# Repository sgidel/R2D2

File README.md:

Repository for R2D2 remote control and management

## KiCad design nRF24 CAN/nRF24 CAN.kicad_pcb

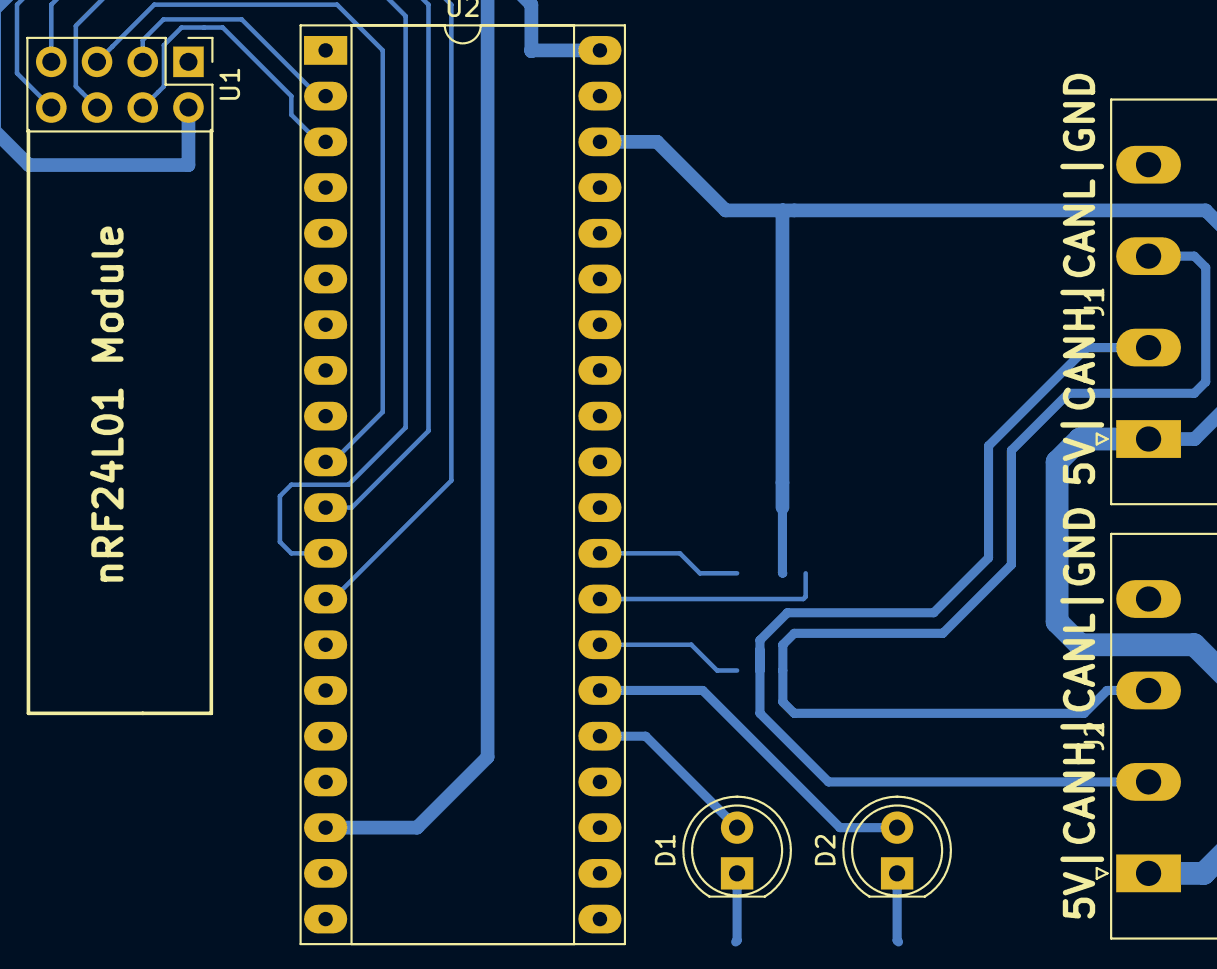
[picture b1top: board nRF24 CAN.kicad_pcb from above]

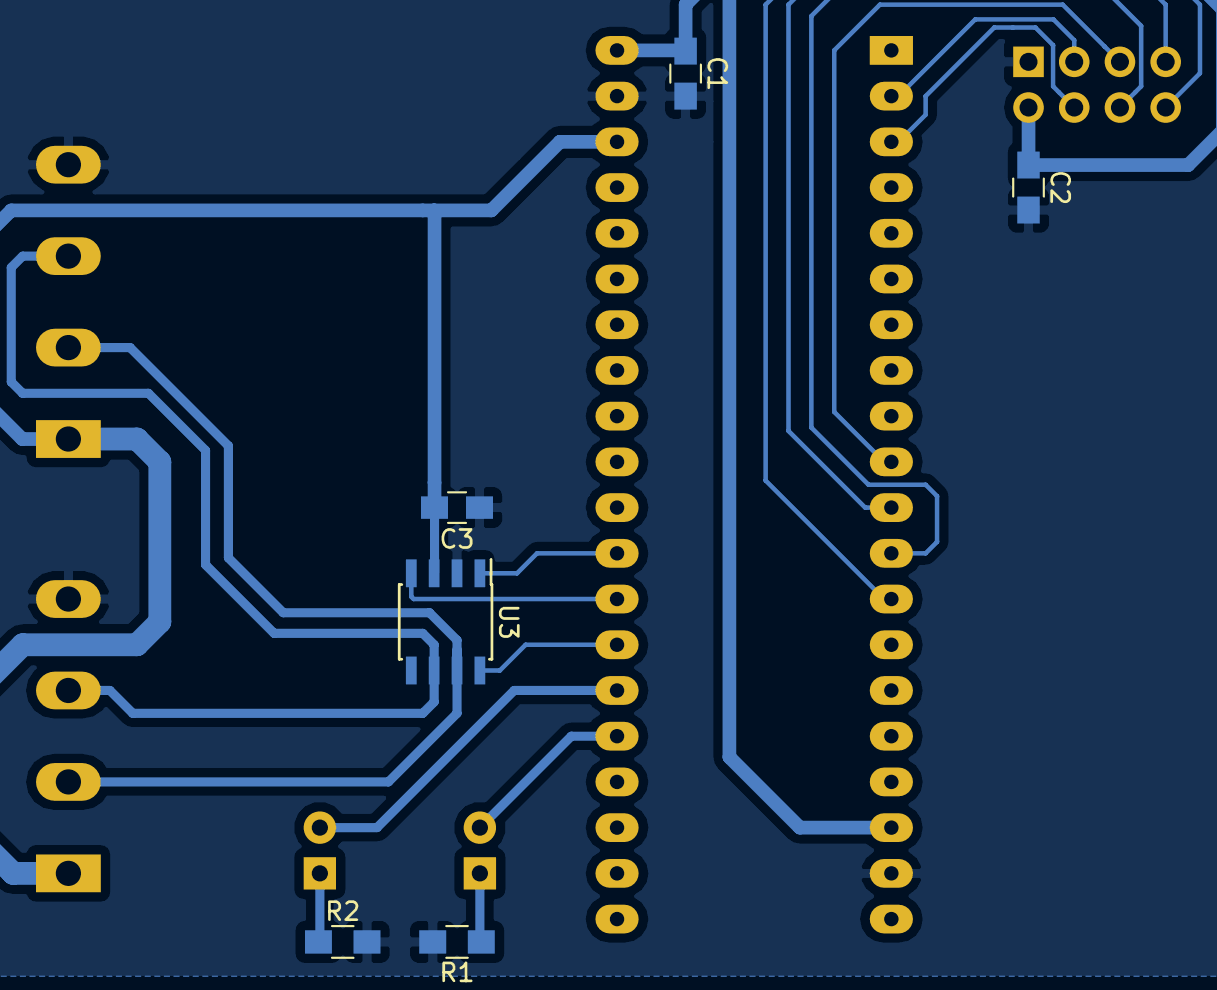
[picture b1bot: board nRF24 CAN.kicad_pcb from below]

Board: 2 copper layers, 12 parts (6 on the bottom side), 18 nets.

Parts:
C1, C2, C3: 0.1u; C_0805_HandSoldering
D1, D2: LED; LED_D5.0mm
J1: CAN IN; PhoenixContact_MSTBA-G_04x5.08mm_Angled
J2: CAN OUT; PhoenixContact_MSTBA-G_04x5.08mm_Angled
R1, R2: 220; R_0805_HandSoldering
U1: nRF24L01; Pin_Header_Straight_2x04_Pitch2.54mm
U2: STM32F103C8T6-MOD; DIP-40_W15.24mm_Socket_LongPads
U3: MCP2557FD; SOIC-8_3.9x4.9mm_Pitch1.27mm

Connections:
+3V3: C1.1, C2.1, U1.2, U2.18, U2.40
+5V: C3.2, J1.1, J2.1, U2.38, U3.3
GND: C1.2, C2.2, C3.1, J1.4, J2.4, R1.2, R2.2, U1.1, U2.19, U2.39, U3.2
unnamed: D1.1, R1.1
unnamed: D1.2, U2.25
unnamed: D2.1, R2.1
unnamed: D2.2, U2.26
unnamed: J1.2, J2.2, U3.7
unnamed: J1.3, J2.3, U3.6
unnamed: U1.3, U2.2
unnamed: U1.4, U2.3
unnamed: U1.5, U2.10
unnamed: U1.6, U2.12
unnamed: U1.7, U2.11
unnamed: U1.8, U2.13
unnamed: U2.27, U3.8
unnamed: U2.28, U3.4
unnamed: U2.29, U3.1

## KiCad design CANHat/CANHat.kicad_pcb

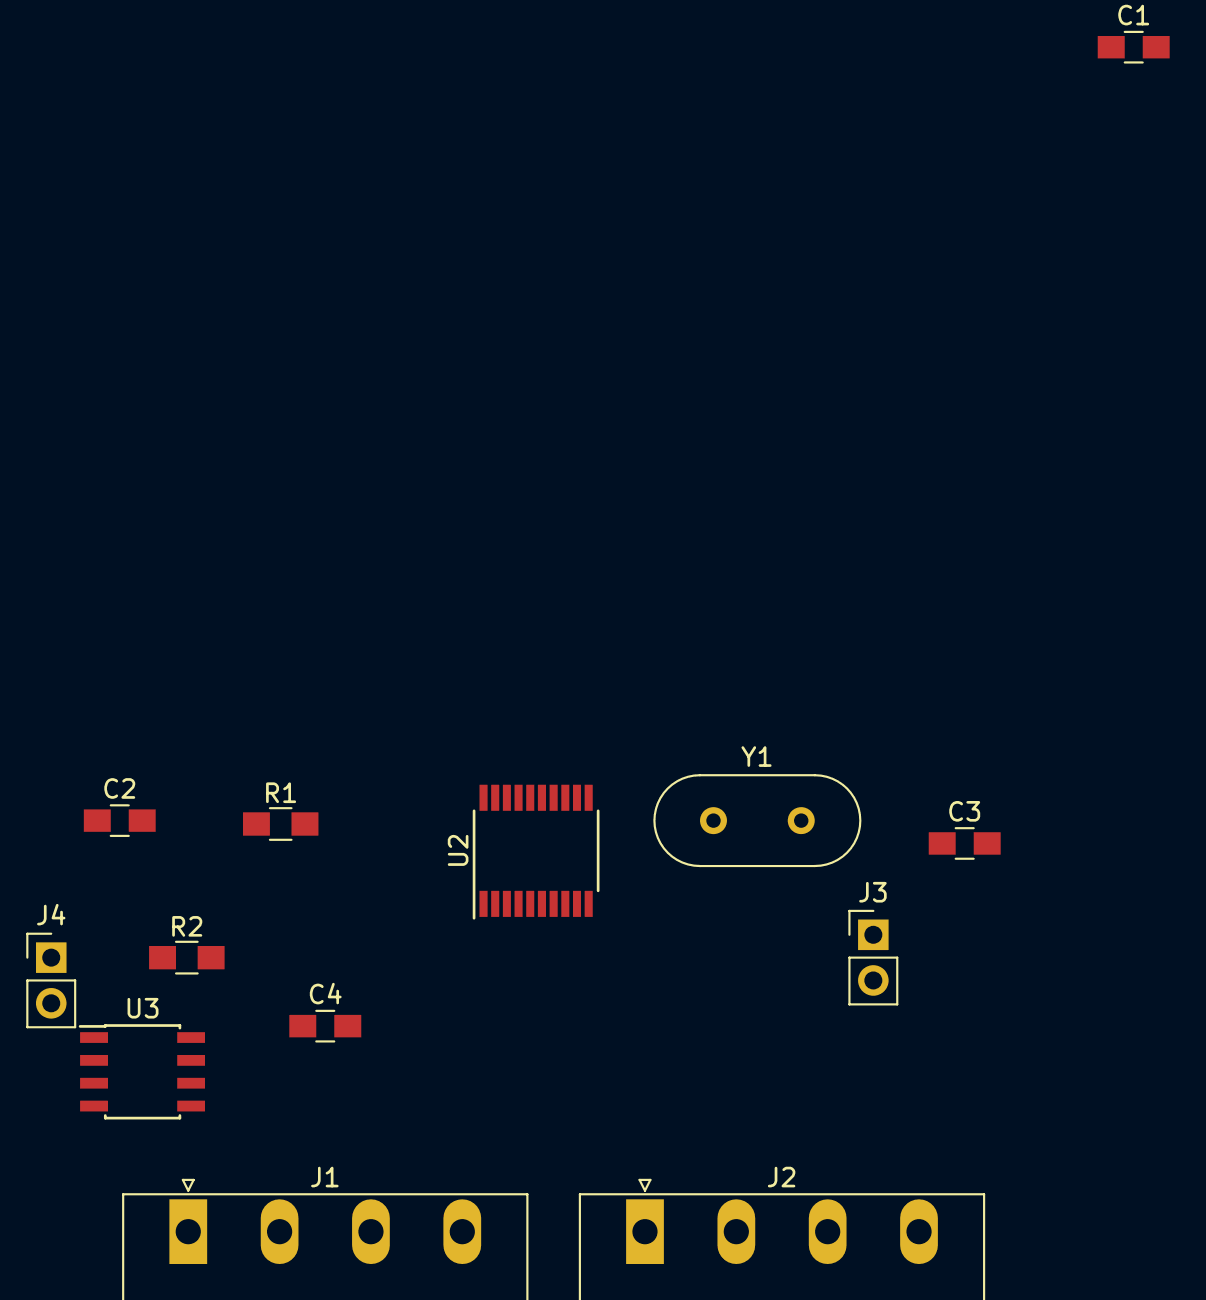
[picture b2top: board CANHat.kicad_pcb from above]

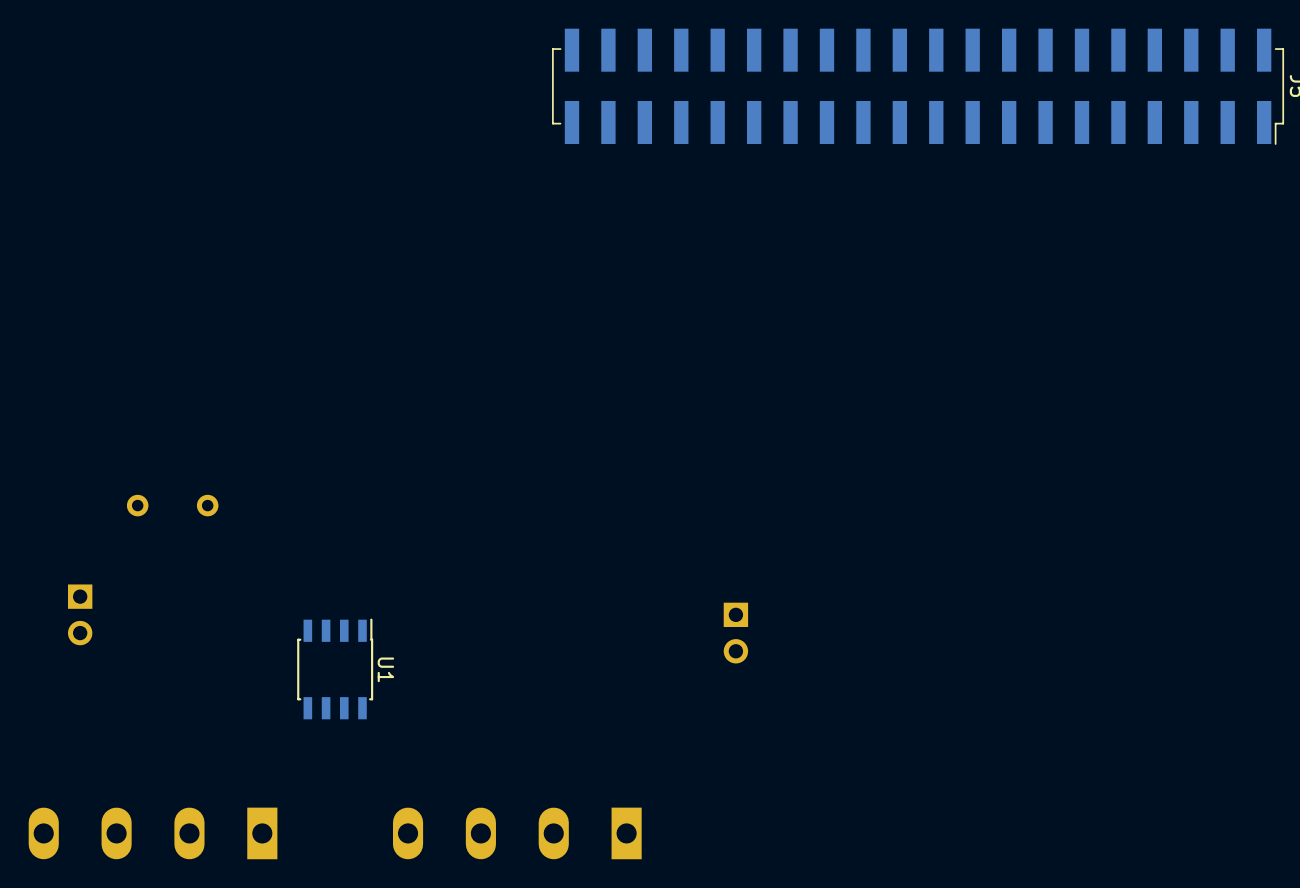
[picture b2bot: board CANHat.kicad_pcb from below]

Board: 2 copper layers, 15 parts (2 on the bottom side), 19 nets, no tracks yet.

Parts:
C1, C2: 0.1u; C_0805_HandSoldering
C3, C4: 18p; C_0805_HandSoldering
J1: CAN IN; PhoenixContact_MSTBA-G_04x5.08mm_Angled
J2: CAN OUT; PhoenixContact_MSTBA-G_04x5.08mm_Angled
J3: POWER; Pin_Header_Straight_1x02_Pitch2.54mm
J4: ~WP; Pin_Header_Straight_1x02_Pitch2.54mm
J5: GPIO; Socket_Strip_Straight_2x20_Pitch2.54mm_SMD
R1: 10K; R_0805_HandSoldering
R2: 1K; R_0805_HandSoldering
U1: TJA1051T; SOIC-8_3.9x4.9mm_Pitch1.27mm
U2: MCP2515-E/ST; TSSOP-20_4.4x6.5mm_Pitch0.65mm
U3: 24LC32; SOIC-8_3.9x4.9mm_Pitch1.27mm
Y1: 16MHz; Crystal_HC49-4H_Vertical

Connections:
+3V3: C2.2, J5.1, J5.17, R1.2, R2.1, U2.20, U3.8
+5V: C1.2, J3.2, J5.2, J5.4, U1.3
/MISO: J5.21, U2.17
/MOSI: J5.19, U2.16
/SCK: J5.23, U2.14
/~CS: J5.24, U2.18
/~INT: J5.22, U2.13
GND: C1.1, C2.1, C3.1, C4.1, J1.1, J2.1, J4.2, J5.6, J5.9, J5.14, J5.20, J5.25, J5.30, J5.34, J5.39, U1.2, U1.8, U2.10, U3.1, U3.2, U3.3, U3.4
unnamed: C3.2, U2.8, Y1.1
unnamed: C4.2, U2.9, Y1.2
unnamed: J1.2, J2.2, U1.6
unnamed: J1.3, J2.3, U1.7
unnamed: J4.1, R2.2, U3.7
unnamed: J5.27, U3.5
unnamed: J5.28, U3.6
unnamed: R1.1, U2.19
unnamed: U1.1, U2.1
unnamed: U1.4, U2.2
VCC: J1.4, J2.4, J3.1

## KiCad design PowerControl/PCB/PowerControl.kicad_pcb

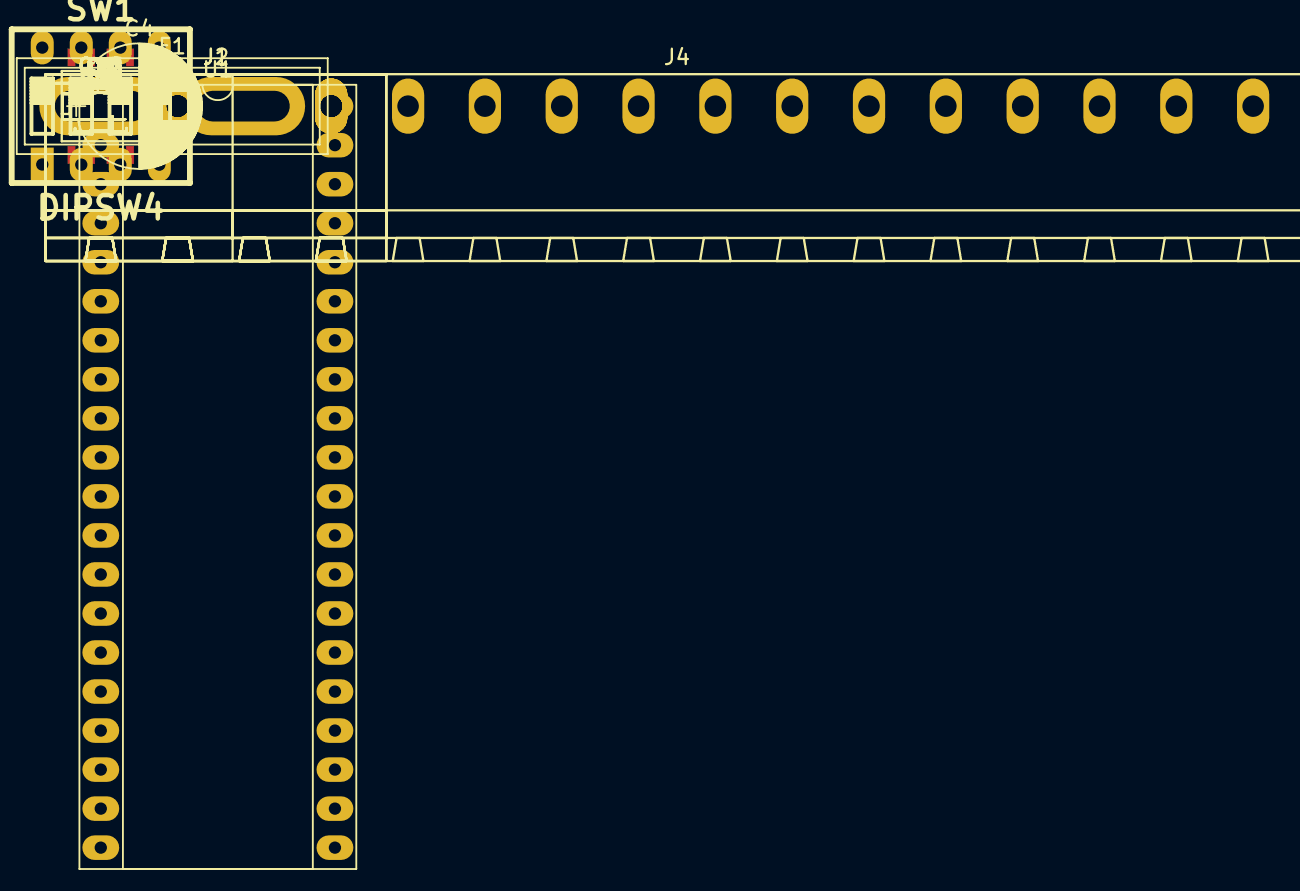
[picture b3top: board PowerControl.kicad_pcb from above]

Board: 2 copper layers, 64 parts (0 on the bottom side), 57 nets, no tracks yet.

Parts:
C1, C2, C3: 0.1u; C_0805_HandSoldering
C4: 100u; CP_Radial_D8.0mm_P5.00mm
D1, D2, D3, D4, D5, D6, D7, D8, D9, D10: LED; LED_1206
F1: 25A; BladeFuse-CarType
J1: CAN IN; PhoenixContact_MSTBA-G_04x5.00mm_Angled
J2: CAN OUT; PhoenixContact_MSTBA-G_04x5.00mm_Angled
J3: 12V; PhoenixContact_MSTBA-G_02x5.00mm_Angled
J4: OUTPUT; PhoenixContact_MSTBA-G_16x5.00mm_Angled
Q1, Q2, Q3, Q4, Q5, Q6, Q7, Q8: MMBT3904; SOT-23
Q9, Q10, Q11, Q12, Q13, Q14, Q15, Q16: IRF7606PBF; MSOP-8_3x3mm_Pitch0.65mm
R1, R2, R3, R4, R5, R6, R7, R8, R9, R10: 220; R_0805_HandSoldering
R11, R12, R13, R14, R15, R16, R17, R18, R19, R20, R21, R22, R23, R24, R25, R26: 1K; R_0805_HandSoldering
SW1: DIPSW4; dip_4-300
U1: STM32F103C8T6-MOD; DIP-40_W15.24mm_Socket_LongPads
U2: MCP2557FD; SOIC-8-N

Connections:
+5V: C1.1, C2.1, C3.1, C4.1, J1.1, J2.1, SW1.5, SW1.6, SW1.7, SW1.8, U1.38, U2.3
+12V: F1.2, J3.1
/CANH: J1.2, J2.2, U2.7
/CANL: J1.3, J2.3, U2.6
/RXLED: D10.2, U1.25
/TXLED: D9.2, U1.26
CANRX: U1.28, U2.4
CANTX: U1.29, U2.1
CH1: D1.2, R11.2, U1.5
CH2: D2.2, R12.2, U1.6
CH3: D3.2, R13.2, U1.7
CH4: D4.2, R14.2, U1.8
CH5: D5.2, R15.2, U1.11
CH6: D6.2, R16.2, U1.12
CH7: D7.2, R17.2, U1.13
CH8: D8.2, R18.2, U1.14
GND: C1.2, C2.2, C3.2, C4.2, J1.4, J2.4, J3.2, J4.2, J4.4, J4.6, J4.8, J4.10, J4.12, J4.14, J4.16, Q1.2, Q2.2, Q3.2, Q4.2, Q5.2, Q6.2, Q7.2, Q8.2, R1.1, R2.1, R3.1, R4.1, R5.1, R6.1, R7.1, R8.1, R9.1, R10.1, U1.19, U1.20, U1.39, U2.2
INH: U1.27, U2.8
unnamed: D1.1, R1.2
unnamed: D2.1, R2.2
unnamed: D3.1, R3.2
unnamed: D4.1, R4.2
unnamed: D5.1, R5.2
unnamed: D6.1, R6.2
unnamed: D7.1, R7.2
unnamed: D8.1, R8.2
unnamed: D9.1, R9.2
unnamed: D10.1, R10.2
unnamed: F1.1, Q9.1, Q9.2, Q9.3, Q10.1, Q10.2, Q10.3, Q11.1, Q11.2, Q11.3, Q12.1, Q12.2, Q12.3, Q13.1, Q13.2, Q13.3, Q14.1, Q14.2, Q14.3, Q15.1, Q15.2, Q15.3, Q16.1, Q16.2, Q16.3, R19.2, R20.2, R21.2, R22.2, R23.2, R24.2, R25.2, R26.2
unnamed: J4.1, Q9.5, Q9.6, Q9.7, Q9.8
unnamed: J4.3, Q10.5, Q10.6, Q10.7, Q10.8
unnamed: J4.5, Q11.5, Q11.6, Q11.7, Q11.8
unnamed: J4.7, Q12.5, Q12.6, Q12.7, Q12.8
unnamed: J4.9, Q13.5, Q13.6, Q13.7, Q13.8
unnamed: J4.11, Q14.5, Q14.6, Q14.7, Q14.8
unnamed: J4.13, Q15.5, Q15.6, Q15.7, Q15.8
unnamed: J4.15, Q16.5, Q16.6, Q16.7, Q16.8
unnamed: Q1.1, R11.1
unnamed: Q1.3, Q9.4, R19.1
unnamed: Q2.1, R12.1
unnamed: Q3.1, R13.1
unnamed: Q4.1, R14.1
unnamed: Q5.1, R15.1
unnamed: Q6.1, R16.1
unnamed: Q7.1, R17.1
unnamed: Q8.1, R18.1
unnamed: Q2.3, Q10.4, R20.1
unnamed: Q3.3, Q11.4, R21.1
unnamed: Q4.3, Q12.4, R22.1
unnamed: Q5.3, Q13.4, R23.1
unnamed: Q6.3, Q14.4, R24.1
unnamed: Q7.3, Q15.4, R25.1
unnamed: Q8.3, Q16.4, R26.1
unnamed: SW1.1, U1.32
unnamed: SW1.2, U1.33
unnamed: SW1.3, U1.34
unnamed: SW1.4, U1.35

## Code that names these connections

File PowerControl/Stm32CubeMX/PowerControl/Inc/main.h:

/**
  ******************************************************************************
  * File Name          : main.h
  * Description        : This file contains the common defines of the application
  ******************************************************************************
  *
  * COPYRIGHT(c) 2017 STMicroelectronics
  *
  * Redistribution and use in source and binary forms, with or without modification,
  * are permitted provided that the following conditions are met:
  *   1. Redistributions of source code must retain the above copyright notice,
  *      this list of conditions and the following disclaimer.
  *   2. Redistributions in binary form must reproduce the above copyright notice,
  *      this list of conditions and the following disclaimer in the documentation
  *      and/or other materials provided with the distribution.
  *   3. Neither the name of STMicroelectronics nor the names of its contributors
  *      may be used to endorse or promote products derived from this software
  *      without specific prior written permission.
  *
  * THIS SOFTWARE IS PROVIDED BY THE COPYRIGHT HOLDERS AND CONTRIBUTORS "AS IS"
  * AND ANY EXPRESS OR IMPLIED WARRANTIES, INCLUDING, BUT NOT LIMITED TO, THE
  * IMPLIED WARRANTIES OF MERCHANTABILITY AND FITNESS FOR A PARTICULAR PURPOSE ARE
  * DISCLAIMED. IN NO EVENT SHALL THE COPYRIGHT HOLDER OR CONTRIBUTORS BE LIABLE
  * FOR ANY DIRECT, INDIRECT, INCIDENTAL, SPECIAL, EXEMPLARY, OR CONSEQUENTIAL
  * DAMAGES (INCLUDING, BUT NOT LIMITED TO, PROCUREMENT OF SUBSTITUTE GOODS OR
  * SERVICES; LOSS OF USE, DATA, OR PROFITS; OR BUSINESS INTERRUPTION) HOWEVER
  * CAUSED AND ON ANY THEORY OF LIABILITY, WHETHER IN CONTRACT, STRICT LIABILITY,
  * OR TORT (INCLUDING NEGLIGENCE OR OTHERWISE) ARISING IN ANY WAY OUT OF THE USE
  * OF THIS SOFTWARE, EVEN IF ADVISED OF THE POSSIBILITY OF SUCH DAMAGE.
  *
  ******************************************************************************
  */
/* Define to prevent recursive inclusion -------------------------------------*/
#ifndef __MAIN_H
#define __MAIN_H
  /* Includes ------------------------------------------------------------------*/

/* USER CODE BEGIN Includes */

/* USER CODE END Includes */

/* Private define ------------------------------------------------------------*/

#define USRLED1_Pin GPIO_PIN_13
#define USRLED1_GPIO_Port GPIOC
#define RXLED_Pin GPIO_PIN_8
#define RXLED_GPIO_Port GPIOA
#define TXLED_Pin GPIO_PIN_9
#define TXLED_GPIO_Port GPIOA
#define INH_Pin GPIO_PIN_10
#define INH_GPIO_Port GPIOA
#define ADDR0_Pin GPIO_PIN_4
#define ADDR0_GPIO_Port GPIOB
#define ADDR1_Pin GPIO_PIN_5
#define ADDR1_GPIO_Port GPIOB
#define ADDR2_Pin GPIO_PIN_6
#define ADDR2_GPIO_Port GPIOB
#define ADDR3_Pin GPIO_PIN_7
#define ADDR3_GPIO_Port GPIOB

/* USER CODE BEGIN Private defines */

/* USER CODE END Private defines */

/**
  * @}
  */ 

/**
  * @}
*/ 

#endif /* __MAIN_H */
/************************ (C) COPYRIGHT STMicroelectronics *****END OF FILE****/

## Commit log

2017-03-05 =Inital Comit
2017-03-05 Cleaned up Directory and added README
2017-04-25 Added STM32 CANBus Example
2017-04-25 Fix CAN Code include
2017-04-25 Added Gitignore for binaries
2017-04-25 Really, actually fix gitignore
2017-04-25 Removed Binaries
2017-04-25 Removed Eclipse binary directories
2017-04-25 Added Device tree patch for Alwinner A20 Boards
2017-05-18 Started work on Power Controller
2017-10-01 Add code for neopixels and Simon game
2017-10-14 Add nrf24l01 pcb library
2017-10-14 Add Julio's Code
